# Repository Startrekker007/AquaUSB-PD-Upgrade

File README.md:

# AquaUSB-PD-Upgrade
My 5V USB supply on my car overheated and blew up, replacing it with a Gigachad beastmode USB power delivery compatible USB-C output (with an additional USB-A for other devices)

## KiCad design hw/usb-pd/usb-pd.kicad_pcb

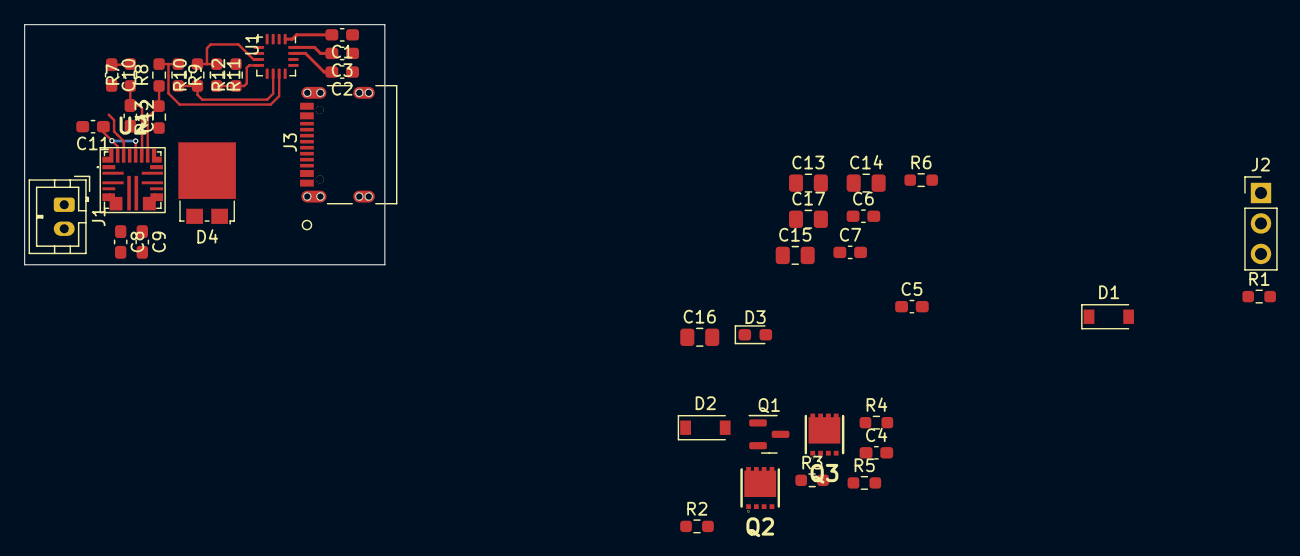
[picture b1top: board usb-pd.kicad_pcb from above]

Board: 4 copper layers, 30.0 x 20.0 mm, 43 parts (1 on the bottom side), 31 nets.

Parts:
C1, C2, C3: 1uF 25V; C_0603_1608Metric_Pad1.08x0.95mm_HandSolder
C4: 10UF 35V; C_0603_1608Metric_Pad1.08x0.95mm_HandSolder
C5, C6, C7, C11: 4.7uF 25V; C_0603_1608Metric_Pad1.08x0.95mm_HandSolder
C8, C9: 0.1uF 16V; C_0603_1608Metric_Pad1.08x0.95mm_HandSolder
C10: Cc; C_0603_1608Metric_Pad1.08x0.95mm_HandSolder
C12: Cf; C_0603_1608Metric_Pad1.08x0.95mm_HandSolder
C13, C14, C15, C16, C17: 22uF 25V; C_0805_2012Metric_Pad1.18x1.45mm_HandSolder
D1, D2: SMF30CA; D_SOD-123
D3: PGD; LED_0603_1608Metric_Pad1.05x0.95mm_HandSolder
D4: V8PL6-M3/86A; TMBS-TO-277A
J1: +BAT; JST_PH_B2B-PH-K_1x02_P2.00mm_Vertical
J2: PGM_I2C; PinHeader_1x03_P2.54mm_Vertical
J3: USB_C_Receptacle_USB2.0; USB4105-GF-A
L1: 10uH 8.4A; BPSC00131380100M00
Q1: BSS138; SOT-23
Q2, Q3: TPCC8105L1Q; TPCC8105,L1Q
R1: 100R; R_0603_1608Metric_Pad0.98x0.95mm_HandSolder
R2: 1k2; R_0603_1608Metric_Pad0.98x0.95mm_HandSolder
R3, R4: 10k; R_0603_1608Metric_Pad0.98x0.95mm_HandSolder
R5: 2k2; R_0603_1608Metric_Pad0.98x0.95mm_HandSolder
R6: 7k5; R_0603_1608Metric_Pad0.98x0.95mm_HandSolder
R7: Rc; R_0603_1608Metric_Pad0.98x0.95mm_HandSolder
R8: Rfbb1; R_0603_1608Metric_Pad0.98x0.95mm_HandSolder
R9: Rfbb2; R_0603_1608Metric_Pad0.98x0.95mm_HandSolder
R10: Rfbb3; R_0603_1608Metric_Pad0.98x0.95mm_HandSolder
R11: Rfbb4; R_0603_1608Metric_Pad0.98x0.95mm_HandSolder
R12: Rfbb5; R_0603_1608Metric_Pad0.98x0.95mm_HandSolder
R13: Rfbt; R_0603_1608Metric_Pad0.98x0.95mm_HandSolder
U1: STUSB4710AQ1; QFN-16-1EP_3x3mm_P0.5mm
U2: MAX25240; MAX25240AFFFVY

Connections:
+BATT: C5.2, C6.2, C7.2, D1.2 (A2), J1.1, R6.1, U2.2 (SUP), U2.3 (SUP), U2.15 (EN)
/USB-PD Negotiator/PDO2: R11.2, R12.1, U1.8 (SEL_PDO2)
/USB-PD Negotiator/PDO3: R10.2, R11.1, U1.7 (SEL_PDO3)
/USB-PD Negotiator/PDO4: R9.2, R10.1, U1.10 (SEL_PDO4)
/USB-PD Negotiator/PDO5: R8.2, R9.1, U1.11 (SEL_PDO5)
/USB-PD Negotiator/SCL: J2.2, U1.4 (SCL)
/USB-PD Negotiator/SDA: J2.1, U1.5 (SDA)
/USB-PD Negotiator/USB_CC1: J3.A5 (CC1), U1.2 (CC1)
/USB-PD Negotiator/USB_CC2: J3.B5 (CC2), U1.3 (CC2)
/USB-PD Negotiator/USB_VBUS: C4.2, D2.2 (A2), J3.A4 (VBUS), J3.B9 (VBUS), Q3.3 (D), U1.12 (VBUS_SENSE)
/USB-PD Negotiator/Vin: C1.2, C13.1, C14.1, C15.1, C16.1, C17.1, D4.1 (K), Q2.3 (D), R2.1, R3.1, R13.1, U1.1 (Vdd), U2.12 (OUT), U2.13 (OUT)
GND: C1.1, C2.1, C3.1, C4.1, C5.1, C6.1, C7.1, C10.2, C11.2, C12.2, C13.2, C14.2, C15.2, C16.2, C17.2, D1.1 (A1), D2.1 (A1), J1.2, J2.3, J3.A1 (GND), J3.B1 (GND), J3.S1 (SHIELD), Q1.2 (S), R12.2, U1.6 (GND), U1.9 (ADDR0), U2.5 (PGND1), U2.6 (PGND1), U2.9 (PGND2), U2.10 (PGND2), U2.19 (SYNC), U2.22 (AGND)
unnamed: C2.2, U1.15 (VREG_1V2)
unnamed: C3.2, U1.16 (VREG_2V7)
unnamed: C8.1, L1.1, U2.7 (LX1)
unnamed: C8.2, U2.1 (BST1)
unnamed: C9.1, D4.2 (A), L1.2, U2.8 (LX2)
unnamed: C9.2, U2.14 (BST2)
unnamed: C10.1, R7.2
unnamed: C11.1, U2.18 (SPS), U2.21 (VCC)
unnamed: C12.1, R7.1, U2.17 (COMP)
unnamed: D3.1 (K), U2.20 (PGOOD)
unnamed: D3.2 (A), R6.2
unnamed: J3.A6 (D+), J3.B6 (D+), R1.2
unnamed: J3.A7 (D-), J3.B7 (D-), R1.1
unnamed: Q1.1 (G), R3.2, U1.13 (VBUS_DISCH)
unnamed: Q1.3 (D), R2.2
unnamed: Q2.1 (G), Q3.1 (G), R4.2, R5.1
unnamed: Q2.2 (S), Q3.2 (S), R4.1
unnamed: R5.2, U1.14 (VBUS_EN_SRC)
unnamed: R8.1, R13.2, U2.16 (FB)

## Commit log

2022-12-25 Using STUSB4710AQ1 as PD controller, and MAX25240A as vrm
2022-12-26 Schematic complete, calculation of components required for MAX25240
2022-12-29 Preliminary PCB layout, calculated compensation filter and feedback network for MAX25240
